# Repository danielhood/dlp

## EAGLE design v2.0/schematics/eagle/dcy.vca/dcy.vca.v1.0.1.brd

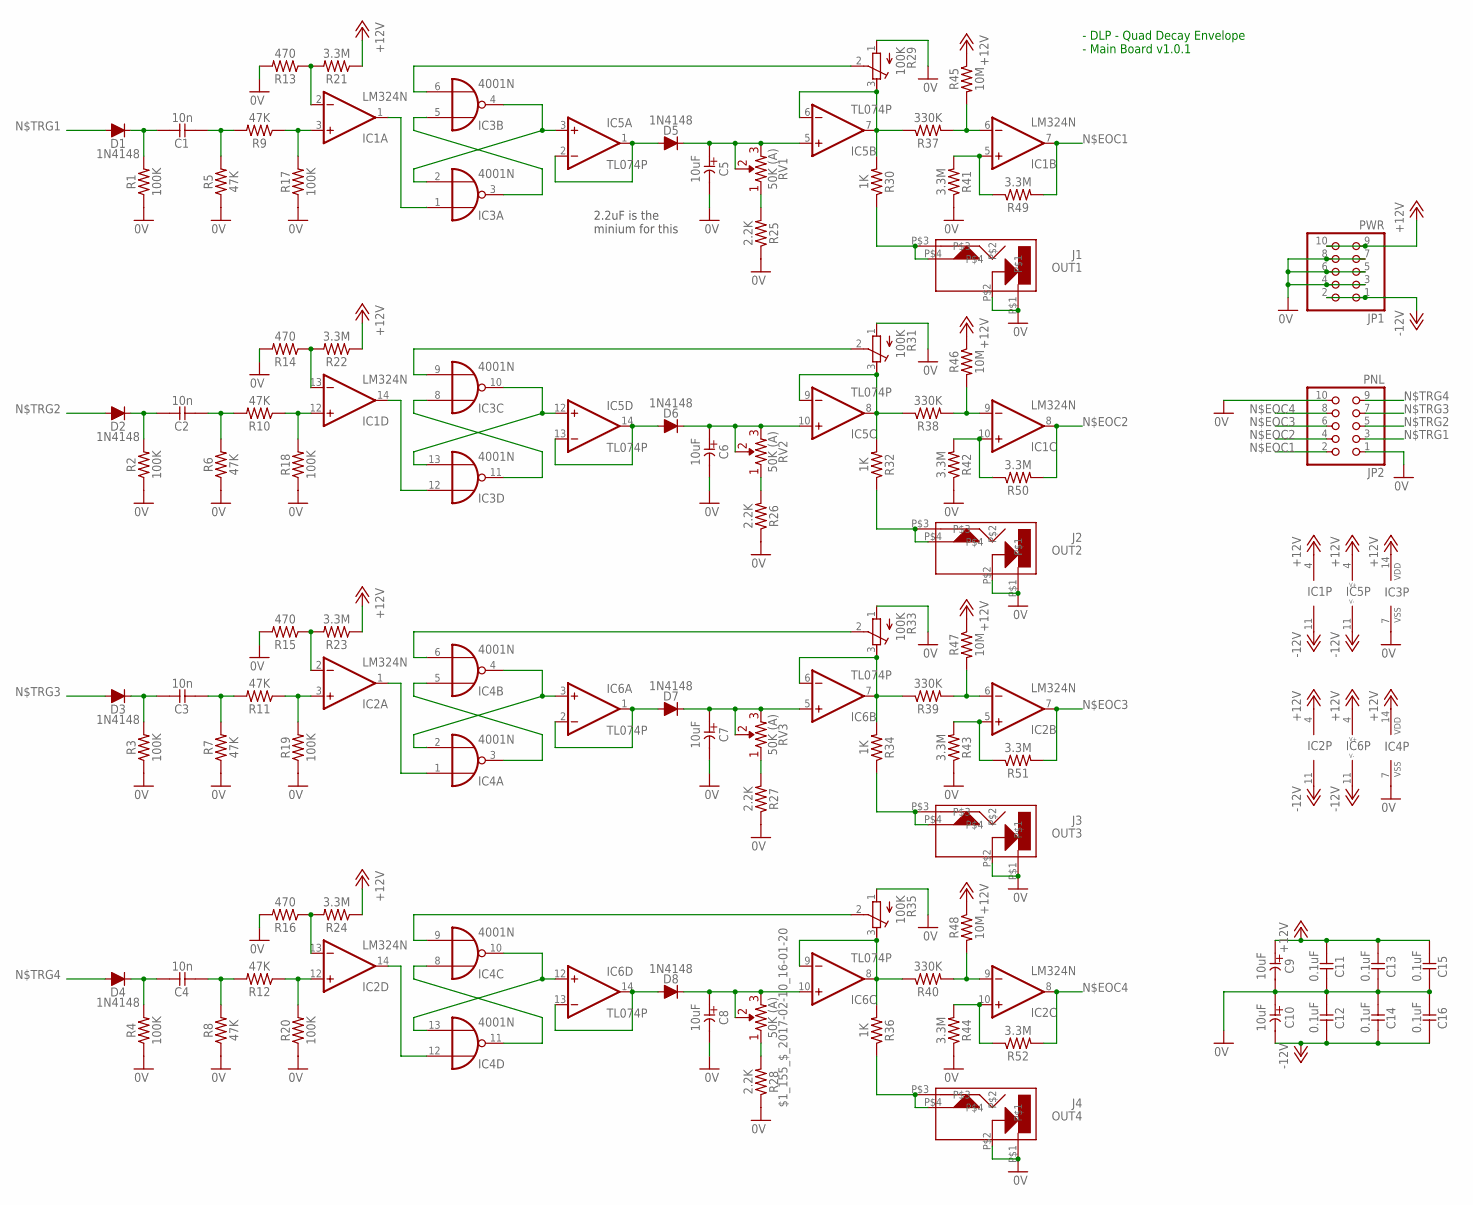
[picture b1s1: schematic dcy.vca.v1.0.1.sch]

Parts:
$1_155_$_2017-02-10_16-01-20: 50K (A); R-VAR
C1, C2, C3, C4: 10n; C025-024X044
C5, C6, C7, C8, C9, C10: 10uF; E2-5
C11, C12, C13, C14, C15, C16: 0.1uF; C025-024X044
D1, D2, D3, D4, D5, D6, D7, D8: 1N4148; DO34-5
IC1, IC2: LM324N; DIL14
IC3, IC4: 4001N; DIL14
IC5, IC6: TL074P; DIL14
J1: OUT1; CL1384
J2: OUT2; CL1384
J3: OUT3; CL1384
J4: OUT4; CL1384
JP1: PWR; 2X05
JP2: PNL; 2X05
R1, R2, R3, R4, R17, R18, R19, R20: 100K; 0207/7
R5, R6, R7, R8, R9, R10, R11, R12: 47K; 0207/7
R13, R14, R15, R16: 470; 0207/7
R21, R22, R23, R24, R41, R42, R43, R44, R49, R50, R51, R52: 3.3M; 0207/7
R25, R26, R27, R28: 2.2K; 0207/7
R29, R31, R33, R35: 100K; RTRIM3339P
R30, R32, R34, R36: 1K; 0207/7
R37, R38, R39, R40: 330K; 0207/7
R45, R46, R47, R48: 10M; 0207/7
RV1, RV2, RV3: 50K (A); R-VAR

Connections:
0V: C5.-, C6.-, C7.-, C8.-, C9.-, C10.+, C11.1, C12.2, C13.1, C14.2, C15.1, C16.2, IC3.7 (VSS), IC4.7 (VSS), J1.P$1, J1.P$2, J2.P$1, J2.P$2, J3.P$1, J3.P$2, J4.P$1, J4.P$2, JP1.3, JP1.4, JP1.5, JP1.6, JP1.7, JP1.8, JP2.1, JP2.10, R1.1, R2.1, R3.1, R4.1, R5.1, R6.1, R7.1, R8.1, R13.2, R14.2, R15.2, R16.2, R17.1, R18.1, R19.1, R20.1, R25.1, R26.1, R27.1, R28.1, R29.1 (A), R31.1 (A), R33.1 (A), R35.1 (A), R41.1, R42.1, R43.1, R44.1
+12V: C9.+, C11.2, C13.2, C15.2, IC1.4 (V+), IC2.4 (V+), IC3.14 (VDD), IC4.14 (VDD), IC5.4 (V+), IC6.4 (V+), JP1.9, JP1.10, R21.1, R22.1, R23.1, R24.1, R45.1, R46.1, R47.1, R48.1
-12V: C10.-, C12.1, C14.1, C16.1, IC1.11 (V-), IC2.11 (V-), IC5.11 (V-), IC6.11 (V-), JP1.1, JP1.2
unnamed: R25.2, RV1.R1 (1)
unnamed: IC1.6 (-IN), R37.2, R45.2
unnamed: IC1.5 (+IN), R41.2, R49.1
unnamed: IC3.3 (O), IC3.5 (I0)
unnamed: IC3.8 (I0), IC3.11 (O)
unnamed: IC3.10 (O), IC3.13 (I1), IC5.12 (+IN)
unnamed: C2.1, D2.C, R2.2
unnamed: C2.2, R6.2, R10.2
unnamed: IC1.12 (+IN), R10.1, R18.2
unnamed: IC3.2 (I1), IC3.4 (O), IC5.3 (+IN)
unnamed: IC1.13 (-IN), R14.1, R22.2
unnamed: D5.A, IC5.1 (OUT), IC5.2 (-IN)
unnamed: C1.1, D1.C, R1.2
unnamed: C1.2, R5.2, R9.2
unnamed: IC1.3 (+IN), R9.1, R17.2
unnamed: IC1.2 (-IN), R13.1, R21.2
unnamed: IC1.1 (OUT), IC3.1 (I0)
unnamed: IC5.6 (-IN), IC5.7 (OUT), R29.3 (E), R30.2, R37.1
unnamed: J1.P$3, J1.P$4, R30.1
unnamed: IC3.6 (I1), R29.2 (S)
unnamed: IC1.14 (OUT), IC3.12 (I0)
unnamed: D6.A, IC5.13 (-IN), IC5.14 (OUT)
unnamed: IC5.8 (OUT), IC5.9 (-IN), R31.3 (E), R32.2, R38.1
unnamed: J2.P$3, J2.P$4, R32.1
unnamed: IC3.9 (I1), R31.2 (S)
unnamed: C6.+, D6.C, IC5.10 (+IN), RV2.R2 (2), RV2.VAR
unnamed: R26.2, RV2.R1 (1)
unnamed: IC1.9 (-IN), R38.2, R46.2
unnamed: IC1.10 (+IN), R42.2, R50.1
unnamed: IC4.3 (O), IC4.5 (I0)
unnamed: IC4.2 (I1), IC4.4 (O), IC6.3 (+IN)
unnamed: C3.1, D3.C, R3.2
unnamed: C3.2, R7.2, R11.2
unnamed: IC2.3 (+IN), R11.1, R19.2
unnamed: IC2.2 (-IN), R15.1, R23.2
unnamed: IC2.1 (OUT), IC4.1 (I0)
unnamed: D7.A, IC6.1 (OUT), IC6.2 (-IN)
unnamed: IC6.6 (-IN), IC6.7 (OUT), R33.3 (E), R34.2, R39.1
unnamed: J3.P$3, J3.P$4, R34.1
unnamed: IC4.6 (I1), R33.2 (S)
unnamed: C7.+, D7.C, IC6.5 (+IN), RV3.R2 (2), RV3.VAR
unnamed: R27.2, RV3.R1 (1)
unnamed: IC2.6 (-IN), R39.2, R47.2
unnamed: IC2.5 (+IN), R43.2, R51.1
unnamed: IC4.8 (I0), IC4.11 (O)
unnamed: IC4.10 (O), IC4.13 (I1), IC6.12 (+IN)
unnamed: C4.1, D4.C, R4.2
unnamed: C4.2, R8.2, R12.2
unnamed: IC2.12 (+IN), R12.1, R20.2
unnamed: C5.+, D5.C, IC5.5 (+IN), RV1.R2 (2), RV1.VAR
unnamed: IC2.13 (-IN), R16.1, R24.2
unnamed: IC2.14 (OUT), IC4.12 (I0)
unnamed: D8.A, IC6.13 (-IN), IC6.14 (OUT)
unnamed: IC6.8 (OUT), IC6.9 (-IN), R35.3 (E), R36.2, R40.1
unnamed: J4.P$3, J4.P$4, R36.1
unnamed: IC4.9 (I1), R35.2 (S)
unnamed: $1_155_$_2017-02-10_16-01-20.R2 (2), $1_155_$_2017-02-10_16-01-20.VAR, C8.+, D8.C, IC6.10 (+IN)
unnamed: $1_155_$_2017-02-10_16-01-20.R1 (1), R28.2
unnamed: IC2.9 (-IN), R40.2, R48.2
unnamed: IC2.10 (+IN), R44.2, R52.1
N$EOC1: IC1.7 (OUT), JP2.2, R49.2
N$EOC2: IC1.8 (OUT), JP2.4, R50.2
N$EOC3: IC2.7 (OUT), JP2.6, R51.2
N$EOC4: IC2.8 (OUT), JP2.8, R52.2
N$TRG1: D1.A, JP2.3
N$TRG2: D2.A, JP2.5
N$TRG3: D3.A, JP2.7
N$TRG4: D4.A, JP2.9

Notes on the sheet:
- DLP - Quad Decay Envelope - Main Board v1.0.1
2.2uF is the minium for this

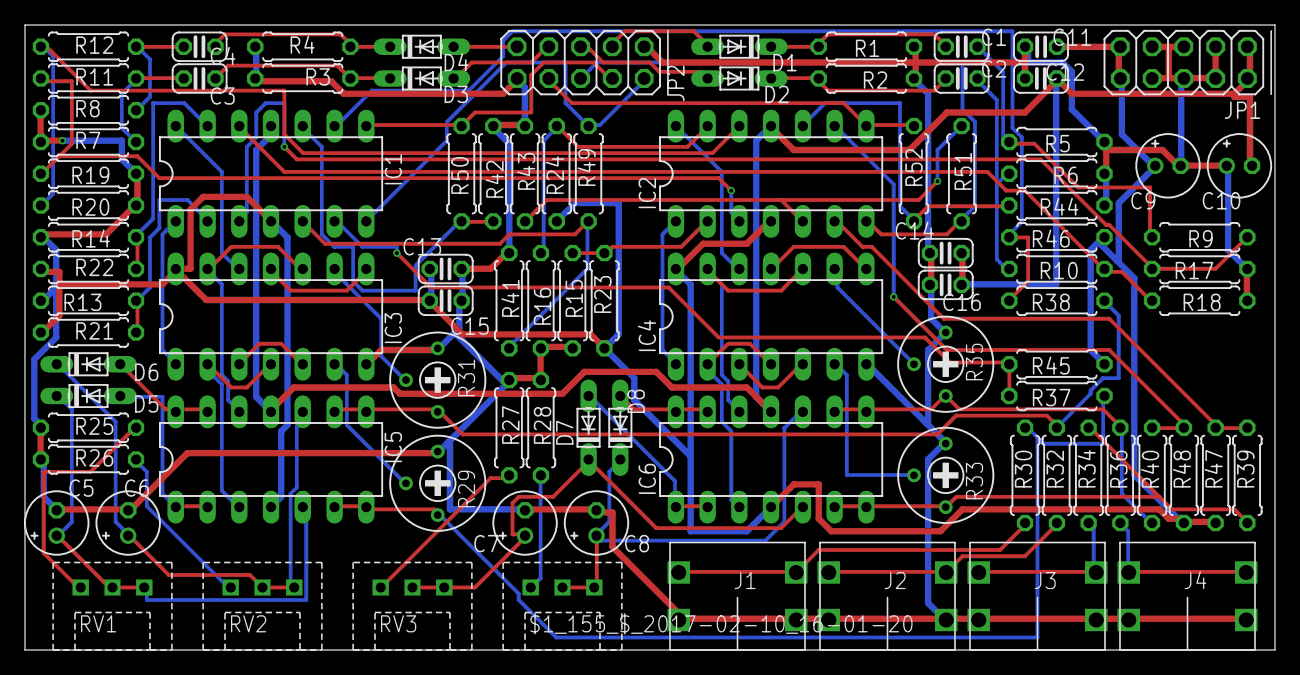
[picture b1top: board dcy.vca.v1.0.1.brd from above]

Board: 2 copper layers, 100.0 x 50.0 mm, 92 parts (0 on the bottom side), 71 nets.

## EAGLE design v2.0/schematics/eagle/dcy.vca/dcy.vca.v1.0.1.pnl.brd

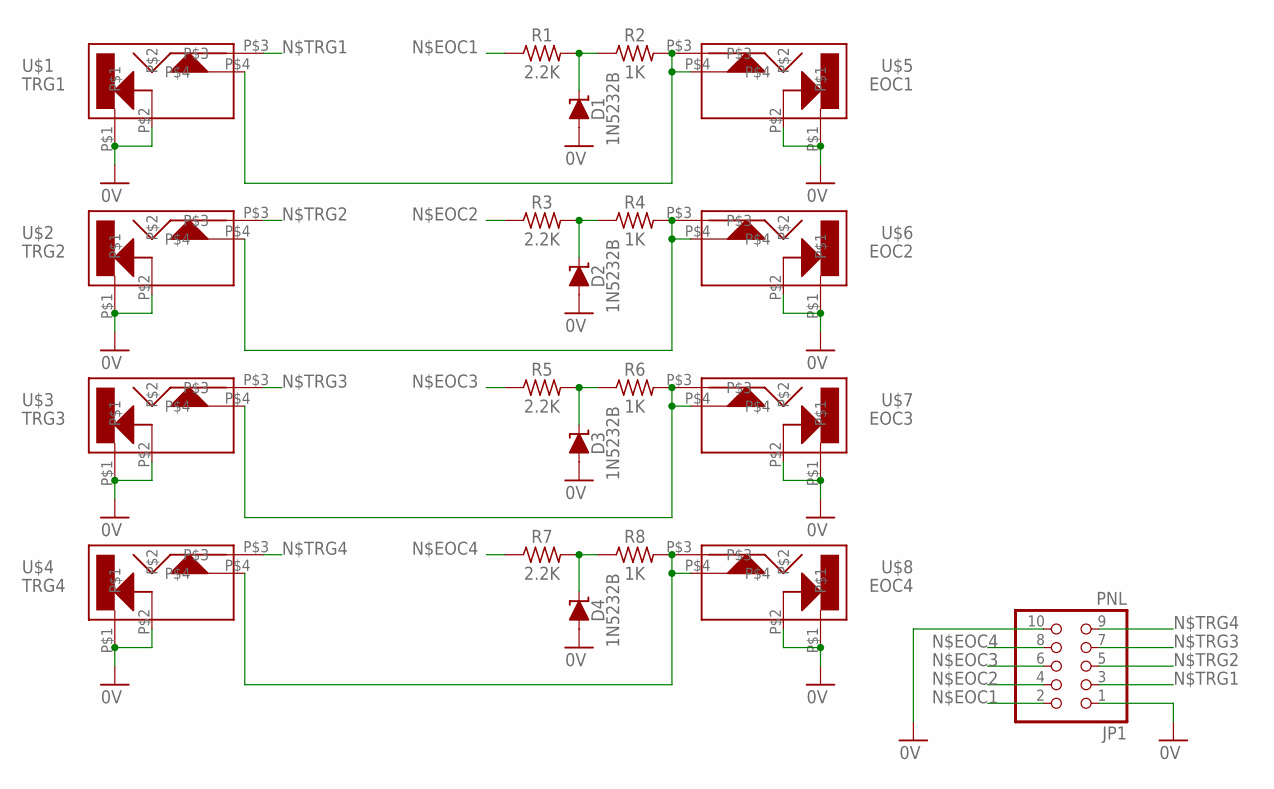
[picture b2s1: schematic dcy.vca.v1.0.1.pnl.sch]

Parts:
D1, D2, D3, D4: 1N5232B; DO34-5
JP1: PNL; 2X05
R1, R3, R5, R7: 2.2K; 0207/7
R2, R4, R6, R8: 1K; 0207/7
U$1: TRG1; CL1384
U$2: TRG2; CL1384
U$3: TRG3; CL1384
U$4: TRG4; CL1384
U$5: EOC1; CL1384
U$6: EOC2; CL1384
U$7: EOC3; CL1384
U$8: EOC4; CL1384

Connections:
0V: D1.A, D2.A, D3.A, D4.A, JP1.1, JP1.10, U$1.P$1, U$1.P$2, U$2.P$1, U$2.P$2, U$3.P$1, U$3.P$2, U$4.P$1, U$4.P$2, U$5.P$1, U$5.P$2, U$6.P$1, U$6.P$2, U$7.P$1, U$7.P$2, U$8.P$1, U$8.P$2
unnamed: D1.C, R1.2, R2.1
unnamed: R2.2, U$1.P$4, U$5.P$3, U$5.P$4
unnamed: D2.C, R3.2, R4.1
unnamed: D3.C, R5.2, R6.1
unnamed: D4.C, R7.2, R8.1
unnamed: R4.2, U$2.P$4, U$6.P$3, U$6.P$4
unnamed: R6.2, U$3.P$4, U$7.P$3, U$7.P$4
unnamed: R8.2, U$4.P$4, U$8.P$3, U$8.P$4
N$EOC1: JP1.2, R1.1
N$EOC2: JP1.4, R3.1
N$EOC3: JP1.6, R5.1
N$EOC4: JP1.8, R7.1
N$TRG1: JP1.3, U$1.P$3
N$TRG2: JP1.5, U$2.P$3
N$TRG3: JP1.7, U$3.P$3
N$TRG4: JP1.9, U$4.P$3

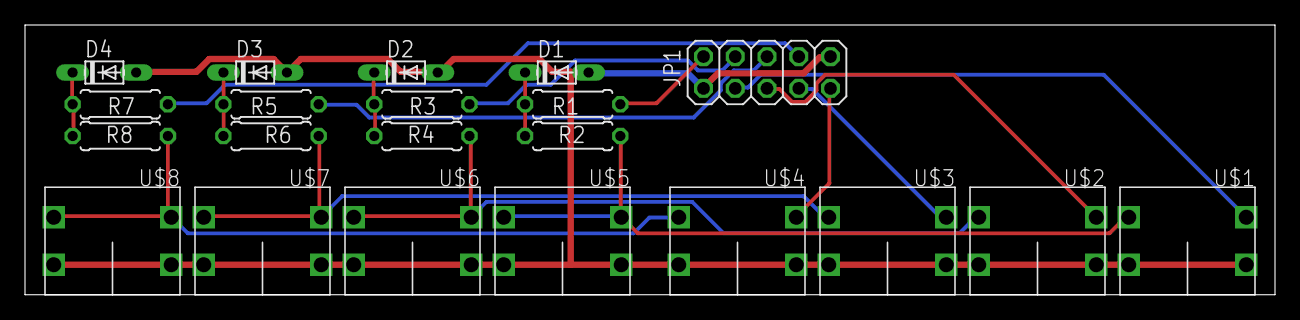
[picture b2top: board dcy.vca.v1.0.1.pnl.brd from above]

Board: 2 copper layers, 100.0 x 21.6 mm, 21 parts (0 on the bottom side), 17 nets.

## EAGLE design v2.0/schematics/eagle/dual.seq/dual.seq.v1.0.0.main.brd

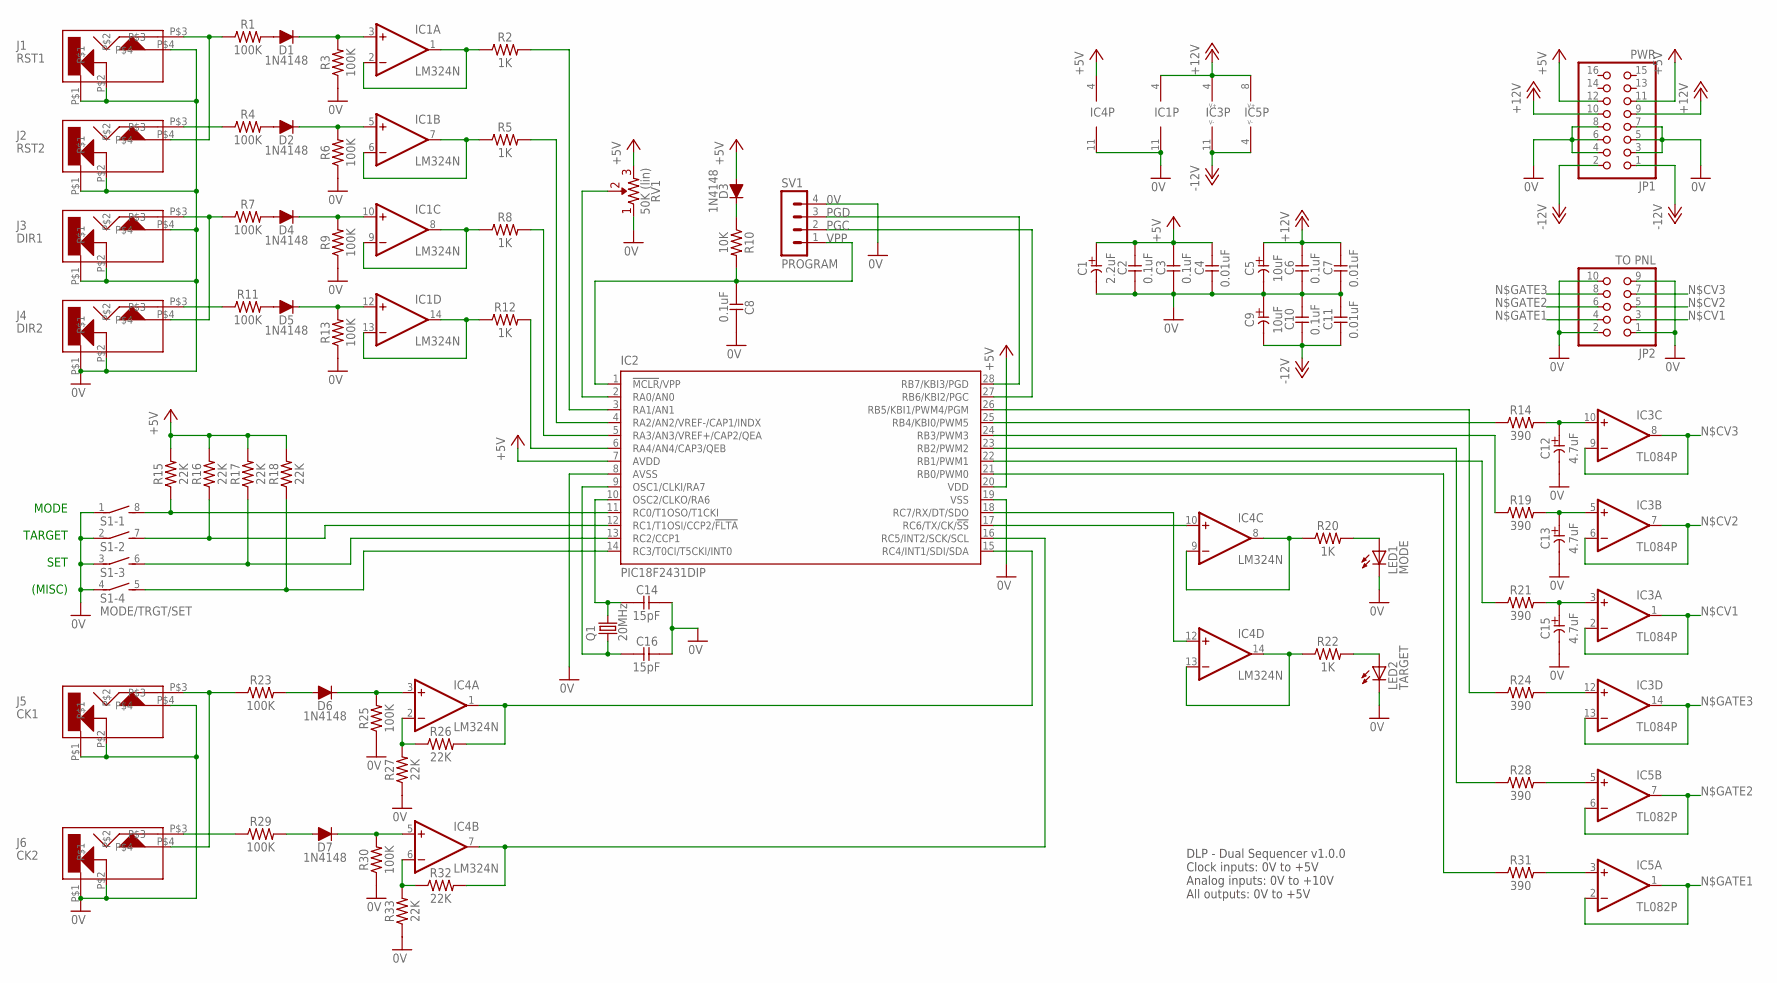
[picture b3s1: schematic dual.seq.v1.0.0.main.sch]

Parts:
C1: 2.2uF; E2-5
C2, C3, C6, C8, C10: 0.1uF; C025-024X044
C4, C7, C11: 0.01uF; C025-024X044
C5, C9: 10uF; E2-5
C12, C13, C15: 4.7uF; E2-5
C14, C16: 15pF; C025-024X044
D1, D2, D3, D4, D5, D6, D7: 1N4148; DO34-5
IC1, IC4: LM324N; DIL14
IC2: PIC18F2431DIP; DIL28-3
IC3: TL084P; DIL14
IC5: TL082P; DIL08
J1: RST1; CL1384
J2: RST2; CL1384
J3: DIR1; CL1384
J4: DIR2; CL1384
J5: CK1; CL1384
J6: CK2; CL1384
JP1: PWR; 2X08
JP2: TO PNL; 2X05
LED1: MODE; LED3MM
LED2: TARGET; LED3MM
Q1: 20MHz; HC49/S
R1, R3, R4, R6, R7, R9, R11, R13, R23, R25, R29, R30: 100K; 0207/7
R2, R5, R8, R12, R20, R22: 1K; 0207/7
R10: 10K; 0207/7
R14, R19, R21, R24, R28, R31: 390; 0207/7
R15, R16, R17, R18, R26, R27, R32, R33: 22K; 0207/7
RV1: 50K (lin); R-VAR
S1: MODE/TRGT/SET; DIP04S
SV1: PROGRAM; MA04-1

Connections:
0V: C1.-, C2.2, C3.2, C4.2, C5.-, C6.2, C7.2, C8.1, C9.+, C10.1, C11.1, C12.-, C13.-, C14.1, C15.-, C16.1, IC1.11 (V-), IC2.8 (AVSS), IC2.19 (VSS), IC4.11 (V-), J1.P$1, J1.P$2, J1.P$4, J2.P$1, J2.P$2, J3.P$1, J3.P$2, J3.P$4, J4.P$1, J4.P$2, J5.P$1, J5.P$2, J5.P$4, J6.P$1, J6.P$2, JP1.3, JP1.4, JP1.5, JP1.6, JP1.7, JP1.8, JP2.1, JP2.2, JP2.9, JP2.10, LED1.K (C), LED2.K (C), R3.1, R6.1, R9.1, R13.1, R25.1, R27.1, R30.1, R33.1, RV1.R1 (1), S1.1, S1.2 (1), S1.3 (1), S1.4 (1), SV1.4
+5V: C1.+, C2.1, C3.1, C4.1, D3.A, IC2.7 (AVDD), IC2.20 (VDD), IC4.4 (V+), JP1.11, JP1.12, R15.2, R16.2, R17.2, R18.2, RV1.R2 (2)
+12V: C5.+, C6.1, C7.1, IC1.4 (V+), IC3.4 (V+), IC5.8 (V+), JP1.9, JP1.10
-12V: C9.-, C10.2, C11.2, IC3.11 (V-), IC5.4 (V-), JP1.1, JP1.2
CV3: C12.+, IC3.10 (+IN), R14.2
unnamed: D3.C, R10.1
unnamed: IC5.3 (+IN), R31.2
unnamed: IC5.5 (+IN), R28.2
unnamed: IC3.12 (+IN), R24.2
unnamed: C15.+, IC3.3 (+IN), R21.2
unnamed: C14.2, IC2.10 (OSC2/CLKO/RA6), Q1.2
unnamed: C13.+, IC3.5 (+IN), R19.2
unnamed: IC2.26 (RB5/KBI1/PWM4/PGM), R24.1
unnamed: IC2.23 (RB2/PWM2), R28.1
unnamed: IC2.21 (RB0/PWM0), R31.1
unnamed: D5.A, R11.2
unnamed: IC2.2 (RA0/AN0), RV1.VAR
unnamed: J1.P$3, J2.P$4, R1.1
unnamed: IC2.3 (RA1/AN1), R2.2
unnamed: D2.A, R4.2
unnamed: IC2.25 (RB4/KBI0/PWM5), R14.1
unnamed: IC2.24 (RB3/PWM3), R19.1
unnamed: IC2.22 (RB1/PWM1), R21.1
unnamed: IC2.15 (RC4/INT1/SDI/SDA), IC4.1 (OUT), R26.2
unnamed: IC2.11 (RC0/T1OSO/T1CKI), R15.1, S1.8 (2)
unnamed: IC2.16 (RC5/INT2/SCK/SCL), IC4.7 (OUT), R32.2
unnamed: D5.C, IC1.12 (+IN), R13.2
unnamed: J3.P$3, J4.P$4, R7.1
unnamed: D4.C, IC1.10 (+IN), R9.2
unnamed: IC2.4 (RA2/AN2/VREF-/CAP1/INDX), R5.2
unnamed: IC2.5 (RA3/AN3/VREF+/CAP2/QEA), R8.2
unnamed: C16.2, IC2.9 (OSC1/CLKI/RA7), Q1.1
unnamed: IC2.12 (RC1/T1OSI/CCP2/!FLTA), R16.1, S1.7 (2)
unnamed: IC2.13 (RC2/CCP1), R17.1, S1.6 (2)
unnamed: J5.P$3, J6.P$4, R23.1
unnamed: IC2.6 (RA4/AN4/CAP3/QEB), R12.2
unnamed: D6.C, IC4.3 (+IN), R25.2
unnamed: D2.C, IC1.5 (+IN), R6.2
unnamed: IC4.13 (-IN), IC4.14 (OUT), R22.1
unnamed: IC4.8 (OUT), IC4.9 (-IN), R20.1
unnamed: IC2.17 (RC6/TX/CK/!SS), IC4.10 (+IN)
unnamed: IC2.18 (RC7/RX/DT/SDO), IC4.12 (+IN)
unnamed: LED1.A, R20.2
unnamed: LED2.A, R22.2
unnamed: D1.C, IC1.3 (+IN), R3.2
unnamed: J6.P$3, R29.1
unnamed: D7.C, IC4.5 (+IN), R30.2
unnamed: IC2.14 (RC3/T0CI/T5CKI/INT0), R18.1, S1.5 (2)
unnamed: D6.A, R23.2
unnamed: D7.A, R29.2
unnamed: D4.A, R7.2
unnamed: D1.A, R1.2
unnamed: J4.P$3, R11.1
unnamed: J2.P$3, R4.1
unnamed: IC1.1 (OUT), IC1.2 (-IN), R2.1
unnamed: IC1.6 (-IN), IC1.7 (OUT), R5.1
unnamed: IC1.8 (OUT), IC1.9 (-IN), R8.1
unnamed: IC1.13 (-IN), IC1.14 (OUT), R12.1
unnamed: IC4.2 (-IN), R26.1, R27.2
unnamed: IC4.6 (-IN), R32.1, R33.2
N$CV1: IC3.1 (OUT), IC3.2 (-IN), JP2.3
N$CV2: IC3.6 (-IN), IC3.7 (OUT), JP2.5
N$CV3: IC3.8 (OUT), IC3.9 (-IN), JP2.7
N$GATE1: IC5.1 (OUT), IC5.2 (-IN), JP2.4
N$GATE2: IC5.6 (-IN), IC5.7 (OUT), JP2.6
N$GATE3: IC3.13 (-IN), IC3.14 (OUT), JP2.8
PGC: IC2.27 (RB6/KBI2/PGC), SV1.2
PGD: IC2.28 (RB7/KBI3/PGD), SV1.3
VPP: C8.2, IC2.1 (!MCLR!/VPP), R10.2, SV1.1

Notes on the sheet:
DLP - Dual Sequencer v1.0.0 Clock inputs: 0V to +5V Analog inputs: 0V to +10V All outputs: 0V to +5V
MODE TARGET SET (MISC)

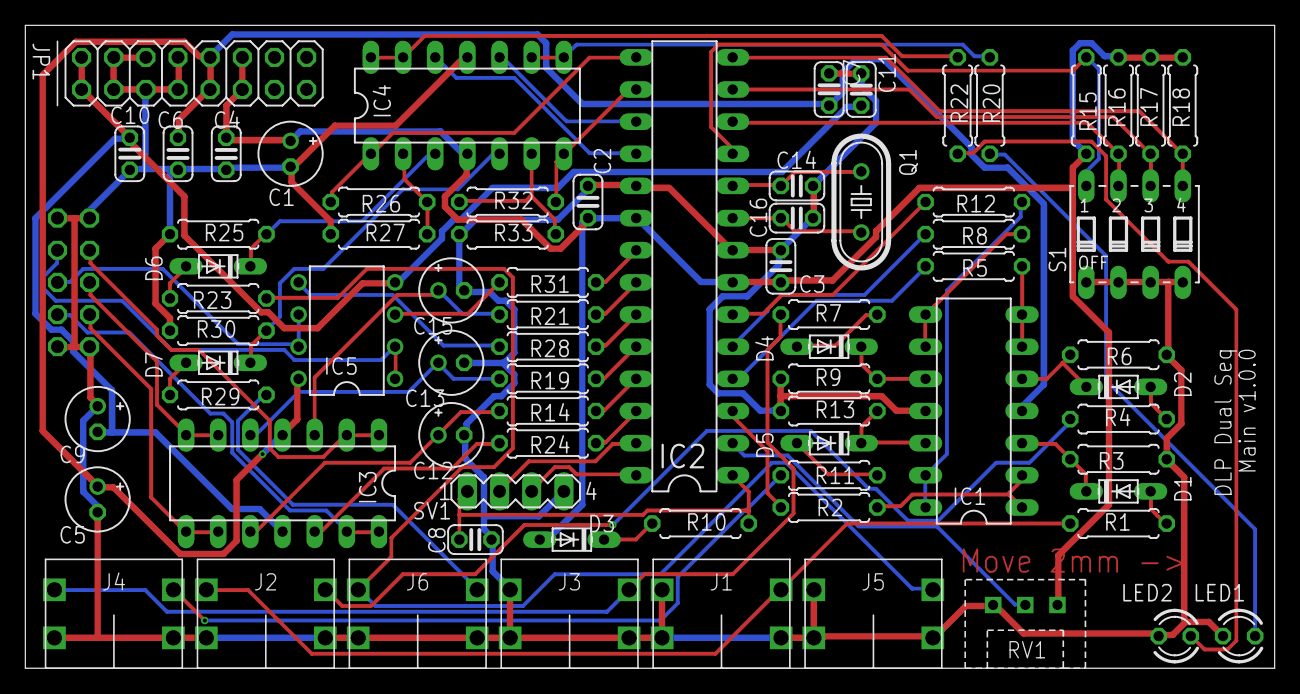
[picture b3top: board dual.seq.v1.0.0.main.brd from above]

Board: 2 copper layers, 98.7 x 50.8 mm, 75 parts (1 on the bottom side), 69 nets.

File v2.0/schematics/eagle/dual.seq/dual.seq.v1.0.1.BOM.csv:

"Qty";"Value";"Device";"Package";"Parts";"Description";"MF";"MPN";"OC_FARNELL";"OC_NEWARK";
"3";"0.01uF";"CC-US025-024X044";"C025-024X044";"C4, C7, C11";"CAPACITOR, US symbol";"";"";"";"";
"5";"0.1uF";"CC-US025-024X044";"C025-024X044";"C2, C3, C6, C8, C10";"CAPACITOR, US symbol";"";"";"";"";
"12";"100K";"R";"0207/7";"R1, R3, R4, R6, R7, R9, R11, R13, R23, R25, R29, R30";"RESISTOR, US symbol";"";"";"";"";
"1";"10K";"R";"0207/7";"R10";"RESISTOR, US symbol";"";"";"";"";
"2";"10uF";"CE-USE2-5";"E2-5";"C5, C9";"ELECTROLYTIC CAPACITOR, US symbol";"";"";"";"";
"2";"15pF";"CC-US025-024X044";"C025-024X044";"C14, C16";"CAPACITOR, US symbol";"";"";"";"";
"6";"1K";"R";"0207/7";"R2, R5, R8, R12, R20, R22";"RESISTOR, US symbol";"";"";"";"";
"7";"1N4148";"1N4148";"DO34-5";"D1, D2, D3, D4, D5, D6, D7";"DIODE";"";"";"";"";
"1";"2.2uF";"CE-USE2-5";"E2-5";"C1";"ELECTROLYTIC CAPACITOR, US symbol";"";"";"";"";
"1";"20MHz";"CRYSTALHC49S";"HC49/S";"Q1";"CRYSTAL";"";"";"1667008";"unknown";
"8";"22K";"R";"0207/7";"R15, R16, R17, R18, R26, R27, R32, R33";"RESISTOR, US symbol";"";"";"";"";
"6";"390";"R";"0207/7";"R14, R19, R21, R24, R28, R31";"RESISTOR, US symbol";"";"";"";"";
"3";"4.7uF";"CE-USE2-5";"E2-5";"C12, C13, C15";"ELECTROLYTIC CAPACITOR, US symbol";"";"";"";"";
"1";"50K (lin)";"R-VAR";"R-VAR";"RV1";"";"";"";"";"";
"1";"CK1";"CL1384";"CL1384";"J5";"";"";"";"";"";
"1";"CK2";"CL1384";"CL1384";"J6";"";"";"";"";"";
"1";"DIR1";"CL1384";"CL1384";"J3";"";"";"";"";"";
"1";"DIR2";"CL1384";"CL1384";"J4";"";"";"";"";"";
"2";"LM324N";"LM324N";"DIL14";"IC1, IC4";"OP AMP";"";"";"";"";
"1";"MODE";"LED3MM";"LED3MM";"LED1";"LED";"";"";"";"";
"1";"MODE/TRGT/SET";"DIP04S";"DIP04S";"S1";"DIL/CODE SWITCH";"";"";"unknown";"unknown";
"1";"PIC18F2431DIP";"PIC18F2431DIP";"DIL28-3";"IC2";"USB Microcontrollers with nanoWatt Technology High-Performance, Enhanced Flash, 28-Pin,";"MICROCHIP";"PIC18F2431-I/SP";"";"";
"1";"PROGRAM";"MA04-1";"MA04-1";"SV1";"PIN HEADER";"";"";"unknown";"unknown";
"1";"PWR";"PINHD-2X8";"2X08";"JP1";"PIN HEADER";"";"";"";"";
"1";"RST1";"CL1384";"CL1384";"J1";"";"";"";"";"";
"1";"RST2";"CL1384";"CL1384";"J2";"";"";"";"";"";
"1";"TARGET";"LED3MM";"LED3MM";"LED2";"LED";"";"";"";"";
"1";"TL082P";"TL082P";"DIL08";"IC5";"OP AMP";"";"";"";"";
"1";"TL084P";"TL084P";"DIL14";"IC3";"OP AMP";"";"";"";"";
"1";"TO PNL";"PINHD-2X5";"2X05";"JP2";"PIN HEADER";"";"";"";"";
"6";"1K";"R";"0207/7";"R1, R2, R3, R4, R5, R6";"RESISTOR, US symbol";"";
"1";"CV1 OUT";"CL1384";"CL1384";"J3";"";"";
"1";"CV2 OUT";"CL1384";"CL1384";"J2";"";"";
"1";"CV3 OUT";"CL1384";"CL1384";"J1";"";"";
"1";"GATE1 OUT";"CL1384";"CL1384";"J6";"";"";
"1";"GATE2 OUT";"CL1384";"CL1384";"J5";"";"";
"1";"GATE3 OUT";"CL1384";"CL1384";"J4";"";"";
"1";"TO MAIN";"PINHD-2X5";"2X05";"JP1";"PIN HEADER";"";

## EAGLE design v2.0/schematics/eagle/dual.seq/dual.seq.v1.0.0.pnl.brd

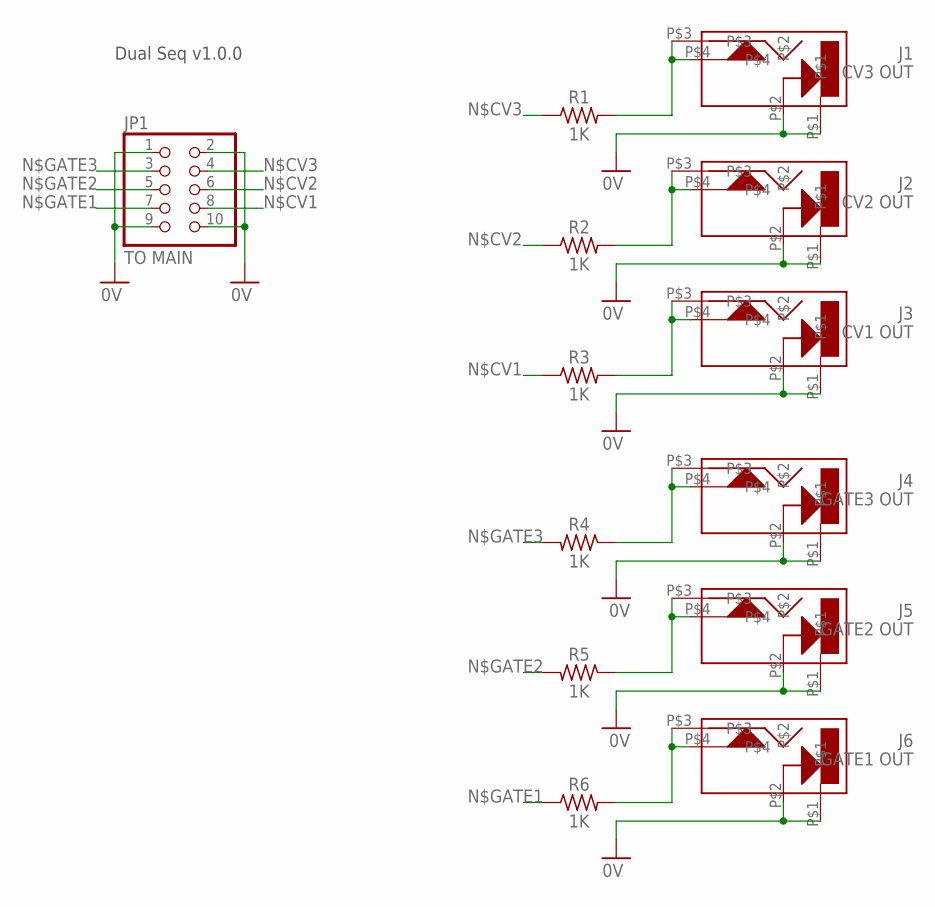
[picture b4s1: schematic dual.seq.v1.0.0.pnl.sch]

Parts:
J1: CV3 OUT; CL1384
J2: CV2 OUT; CL1384
J3: CV1 OUT; CL1384
J4: GATE3 OUT; CL1384
J5: GATE2 OUT; CL1384
J6: GATE1 OUT; CL1384
JP1: TO MAIN; 2X05
R1, R2, R3, R4, R5, R6: 1K; 0207/7

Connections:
0V: J1.P$1, J1.P$2, J2.P$1, J2.P$2, J3.P$1, J3.P$2, J4.P$1, J4.P$2, J5.P$1, J5.P$2, J6.P$1, J6.P$2, JP1.1, JP1.2, JP1.9, JP1.10
unnamed: J6.P$3, J6.P$4, R6.2
unnamed: J5.P$3, J5.P$4, R5.1
unnamed: J4.P$3, J4.P$4, R4.1
unnamed: J3.P$3, J3.P$4, R3.2
unnamed: J2.P$3, J2.P$4, R2.2
unnamed: J1.P$3, J1.P$4, R1.2
N$CV1: JP1.8, R3.1
N$CV2: JP1.6, R2.1
N$CV3: JP1.4, R1.1
N$GATE1: JP1.7, R6.1
N$GATE2: JP1.5, R5.2
N$GATE3: JP1.3, R4.2

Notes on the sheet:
Dual Seq v1.0.0

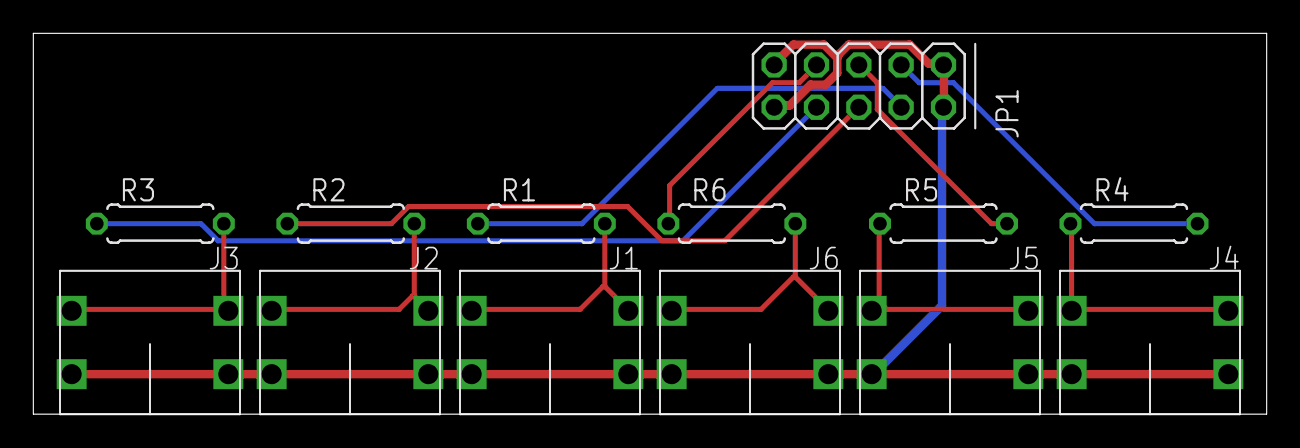
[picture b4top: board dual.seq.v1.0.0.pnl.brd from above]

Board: 2 copper layers, 74.0 x 22.9 mm, 13 parts (0 on the bottom side), 13 nets.

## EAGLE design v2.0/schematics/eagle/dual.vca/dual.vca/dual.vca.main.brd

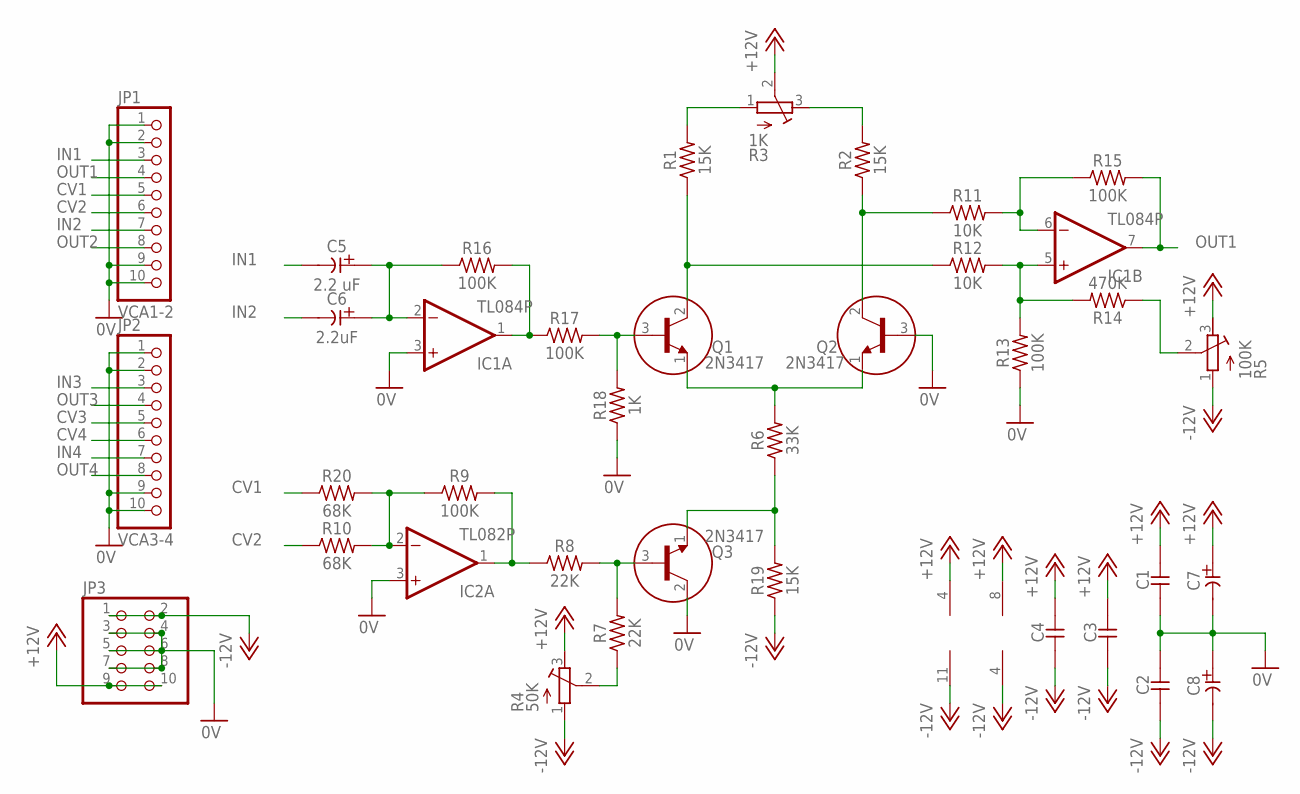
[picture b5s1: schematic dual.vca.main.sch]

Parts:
C1, C2, C3, C4: CC-US025-024X044; C025-024X044
C5: 2.2 uF; E2-5
C6: 2.2uF; E2-5
C7, C8: CE-USE2-5; E2-5
IC1: TL084P; DIL14
IC2: TL082P; DIL08
JP1: VCA1-2; 1X10
JP2: VCA3-4; 1X10
JP3: PINHD-2X5; 2X05
Q1, Q2, Q3: 2N3417; TO92
R1, R2, R19: 15K; 0207/7
R3: 1K; RTRIM3339P
R4: 50K; RTRIM3339P
R5: 100K; RTRIM3339P
R6: 33K; 0207/7
R7, R8: 22K; 0207/7
R9, R13, R15, R16, R17: 100K; 0207/7
R10, R20: 68K; 0207/7
R11, R12: 10K; 0207/7
R14: 470K; 0207/7
R18: 1K; 0207/7

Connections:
0V: C1.2, C2.1, C7.-, C8.+, IC1.3 (+IN), IC2.3 (+IN), JP1.1, JP1.2, JP1.9, JP1.10, JP2.1, JP2.2, JP2.9, JP2.10, JP3.3, JP3.4, JP3.5, JP3.6, JP3.7, JP3.8, Q2.3 (B), Q3.2 (C), R13.1, R18.1
+12V: C1.1, C3.1, C4.1, C7.+, IC1.4 (V+), IC2.8 (V+), JP3.9, JP3.10, R3.2 (S), R4.3 (E), R5.3 (E)
-12V: C2.2, C3.2, C4.2, C8.-, IC1.11 (V-), IC2.4 (V-), JP3.1, JP3.2, R4.1 (A), R5.1 (A), R19.1
CV1: JP1.5, R20.1
CV2: JP1.6, R10.1
CV3: JP2.5
CV4: JP2.6
IN1: C5.-, JP1.3
IN2: C6.-, JP1.7
IN3: JP2.3
IN4: JP2.7
unnamed: C5.+, C6.+, IC1.2 (-IN), R16.1
unnamed: IC1.6 (-IN), R11.2, R15.1
unnamed: IC1.1 (OUT), R16.2, R17.1
unnamed: Q1.3 (B), R17.2, R18.2
unnamed: Q1.2 (C), R1.1, R12.1
unnamed: R1.2, R3.1 (A)
unnamed: R2.2, R3.3 (E)
unnamed: Q2.2 (C), R2.1, R11.1
unnamed: Q1.1 (E), Q2.1 (E), R6.2
unnamed: R5.2 (S), R14.1
unnamed: IC1.5 (+IN), R12.2, R13.2, R14.2
unnamed: Q3.1 (E), R6.1, R19.2
unnamed: Q3.3 (B), R7.2, R8.2
unnamed: R4.2 (S), R7.1
unnamed: IC2.1 (OUT), R8.1, R9.2
unnamed: IC2.2 (-IN), R9.1, R10.2, R20.2
OUT1: IC1.7 (OUT), JP1.4, R15.2
OUT2: JP1.8
OUT3: JP2.4
OUT4: JP2.8

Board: 2 copper layers, 36 parts (0 on the bottom side), 24 nets, no tracks yet.

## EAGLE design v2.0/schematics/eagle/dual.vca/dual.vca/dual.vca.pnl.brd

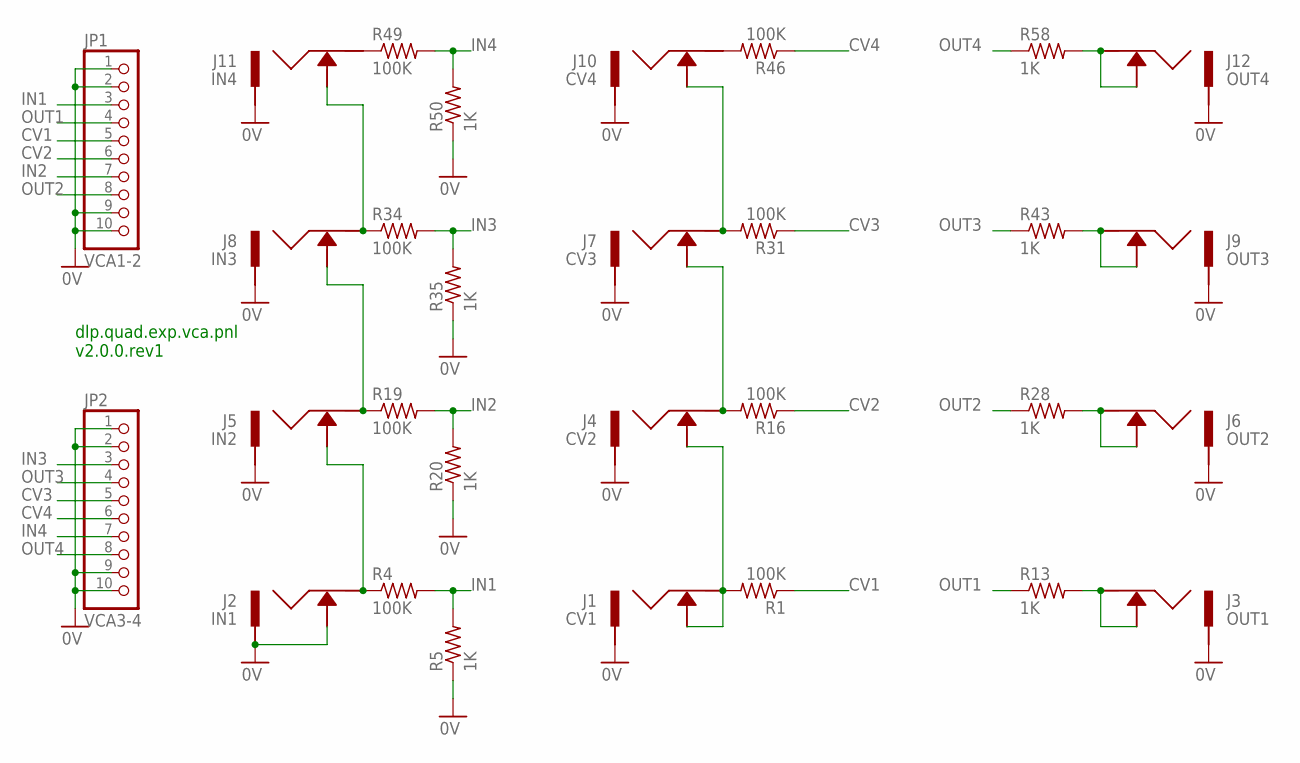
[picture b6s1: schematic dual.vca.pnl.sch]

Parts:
J1: CV1; ACJM-MV35-2S
J2: IN1; ACJM-MV35-2S
J3: OUT1; ACJM-MV35-2S
J4: CV2; ACJM-MV35-2S
J5: IN2; ACJM-MV35-2S
J6: OUT2; ACJM-MV35-2S
J7: CV3; ACJM-MV35-2S
J8: IN3; ACJM-MV35-2S
J9: OUT3; ACJM-MV35-2S
J10: CV4; ACJM-MV35-2S
J11: IN4; ACJM-MV35-2S
J12: OUT4; ACJM-MV35-2S
JP1: VCA1-2; 1X10
JP2: VCA3-4; 1X10
R1, R4, R16, R19, R31, R34, R46, R49: 100K; 0207/7
R5, R13, R20, R28, R35, R43, R50, R58: 1K; 0207/7

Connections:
0V: J1.P$1, J2.P$1, J2.P$2, J3.P$1, J4.P$1, J5.P$1, J6.P$1, J7.P$1, J8.P$1, J9.P$1, J10.P$1, J11.P$1, J12.P$1, JP1.1, JP1.2, JP1.9, JP1.10, JP2.1, JP2.2, JP2.9, JP2.10, R5.1, R20.1, R35.1, R50.1
CV1: JP1.5, R1.1
CV2: JP1.6, R16.1
CV3: JP2.5, R31.1
CV4: JP2.6, R46.1
IN1: JP1.3, R4.2, R5.2
IN2: JP1.7, R19.2, R20.2
IN3: JP2.3, R34.2, R35.2
IN4: JP2.7, R49.2, R50.2
unnamed: J9.P$2, J9.P$3, R43.2
unnamed: J3.P$2, J3.P$3, R13.2
unnamed: J2.P$3, J5.P$2, R4.1
unnamed: J5.P$3, J8.P$2, R19.1
unnamed: J8.P$3, J11.P$2, R34.1
unnamed: J10.P$3, R46.2
unnamed: J7.P$3, J10.P$2, R31.2
unnamed: J4.P$3, J7.P$2, R16.2
unnamed: J1.P$2, J1.P$3, J4.P$2, R1.2
unnamed: J6.P$2, J6.P$3, R28.2
unnamed: J12.P$2, J12.P$3, R58.2
unnamed: J11.P$3, R49.1
OUT1: JP1.4, R13.1
OUT2: JP1.8, R28.1
OUT3: JP2.4, R43.1
OUT4: JP2.8, R58.1

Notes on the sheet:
dlp.quad.exp.vca.pnl v2.0.0.rev1

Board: 2 copper layers, 30 parts (0 on the bottom side), 25 nets, no tracks yet.
